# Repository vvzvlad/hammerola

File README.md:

# hammerola

**English** · [Русский](README.ru.md)

A build system and a viewer for parts that an agent models in code. The agent
writes a `model.py` in CadQuery and pushes the source; the hub computes the
geometry and shows the part in a browser. The person turns it, hides what is in
the way, cuts a section through it, measures it, downloads it as STEP/STL/3MF,
clicks a spot on the model and leaves a note there; the agent reads the notes
with `hammerola comments`, fixes the code and pushes the next revision. No CAD
application is needed anywhere: the model is Python, and the kernel that
computes it is in the hub.

The viewer is there because an STL an agent hands back is a poor thing to
review, and words are a poor way to say what to fix. The page gives what a CAD
gives — each part in its own colour, a section through anything, parts you can
drag aside — and a place to point at: the comment is pinned to that point, with
the camera angle it was written from and, when there is one, a photo of the
printed part. A revision's URL never changes and never expires, so a link is
how a part is shown to someone or sent to a workshop. What goes with the part
publishes on the same page — a KiCad schematic and board with the board's
Gerbers, a PDF, a drawing, a Markdown note, or a file of any other kind — and a
project with no model at all publishes those on their own. The name is from
"pianola" — a mechanism that plays itself.

<!-- Screenshots live in docs/images/ rather than in static/. static/ is the
     viewer payload that ships INSIDE the image, and its `hammerola*` names are
     generated and gitignored; README pictures are drawn by the forge straight
     out of the repository and have no business in a container. -->

## How it works

A model is a directory with a `model.py` in it, in a git repository. A version
of it is a commit: `git push` sends it to the project's own repository on the
hub, which **computes the geometry itself** — in a process of its own, with the
CAD kernel that ships in its image — checks the result, exports STEP/STL/3MF
and serves the whole thing at a URL, and only then lets the push in. Nothing is
built on the laptop, and no forge's CI is involved. A directory with no
`model.py` that lists documents in its `project.json` is published the same way,
except that nothing in it is executed: the documents are the whole build.

Four things follow from that, and between them they are what the tool is for.

**A revision is a commit, and a failed build is a refused push.** The author
pushes the whole repository; the project is the directory holding a
`project.json` with its id, so one repository can carry several projects, each
pushed to its own address. Of each push the hub builds the newest commit that
touched the project's directory, publishes it under the commit's sha and only
then lets git move the branch — a build that fails refuses the push, with its
log in the output, so the branch on the hub never stands on a commit without a
build. Builds published before the hub spoke git were imported into that
history as commits of their own, under their old names.

**A published revision never changes and never expires.** Its URL is served as
immutable, and there is no retention anywhere on the hub — nothing ages out and
no build can be taken back on its own — so a link pasted into a chat shows the
same geometry a year later. `dev` is the other kind of slot: one per variant,
rewritten by every `hammerola build`, no history, never listed, and it is where
the working copy goes while a part is still moving — uncommitted, as a draft
the client pushes beside the branch.

**A variant of a project is a branch.** A ceiling and a wall version of one
case are two branches of its repository, each with its own history, `latest`,
draft and documents, and the page switches between them by the project's title,
for a reader with a link as much as for the owner. `main` is the default
variant and keeps the project's addresses; another branch `b` is under
`/project/<pid>/v/<b>/`, labelled by the `"variant"` key of its own
`project.json`, or by its name.

**Geometry that fails the gate is not published.** Every printable has to be a
valid solid with positive volume, export a watertight mesh and come out as one
body. The `assembled` view is required, it has to show every printable unless
it lists one in `absent_ok` with a reason (an assembly jig is printed but is not
part of the product), and no two parts in it may occupy the same space unless the view says why — with one
standing exemption that is not a declaration: a `mock` is scenery, so a pair
holding one is never measured at all, while `hardware` is asked like anything
else. The `print` view is the bed: printables only, each of them the way up the
catalogue holds it, and each on its own patch of it rather than modelled inside
its neighbour. A build that fails any of it is thrown away whole — `latest` and
`dev` do not move — and what comes back is a failure code and the build's own
log.

**The model is public, the files go with a link that includes them, and the
code is not.** A build's page and the geometry it is drawn from are anonymous:
being given the link is what lets you look at the part. Its STEP/STL/3MF leave
only with the one secret or with a link the owner's Share window made with the
files included. Documents are the exception, on purpose: every file a project
lists as one opens to the link alone, whatever its extension, because that link
is how a revision goes to a workshop or a fab as the complete set — so whoever
has it can download a listed KiCad design whole and edit it. The repository a
revision was built from is on the hub too, but behind the secret, and so is the
list of what exists on the hub at all.

## Publishing a model

The client is `hammerola`, and it lives in this repository on purpose: the
client and the hub share one contract — the routes, the ceilings, the job
states — and it used to be split across two repositories
where no test could see both halves, which is exactly how publication came to be
broken without anyone noticing. It imports nothing outside the standard library,
so whatever `python3` a laptop already has is enough.

**It is installed from the hub**, which serves the three things a first run
needs and asks for no token for any of them — they are the software, identical
on every deployment, and the person downloading them does not have a token yet
by definition:

```bash
mkdir -p ~/.local/bin
curl -fsSL <hub>/start/hammerola -o ~/.local/bin/hammerola && chmod +x ~/.local/bin/hammerola
hammerola login <hub>   # once per machine; the password is prompted for, then the
                        # agent instructions go into ~/.claude/skills/hammerola/
```

The instructions are a directory — a short `SKILL.md` an agent keeps in front of
it and reference files it opens when they apply — so the client installs them
rather than a `curl` per file: it writes the whole directory and removes what
the new version no longer ships.

**On a machine where the client is already installed, that `curl` line comes
first.** A client from before the skill was a directory downloads the archive
and tries to read it as text, and its refusal blames the hub for serving
something that is not utf-8; it is that client being older than the hub, and
replacing it (the `curl` above, or `hammerola update`) is the way out.

**That is how it is installed, checkout or no checkout.** There used to be a second
one — `make client`, which symlinked a `bin/hammerola` script into
`~/.local/bin` — and the two collided under the one name they share: `curl -o`
writes THROUGH a symlink, into its target, so the line above quietly landed the
downloaded zipapp on top of the repository's own file. The link stayed a link,
the command went on working, and the only sign was `git status` calling the
client modified. Both the target and the script are gone. Whoever is *working
on* the client runs it out of the checkout instead — and the whole trick is that
`python3` has to be able to import `hammerola`, which is a statement about where
the command is STARTED, not about where the model is:

```bash
cd <this checkout>
python3 -m hammerola --help                          # the same tool, off the working copy
python3 -m hammerola -C <model dir> status           # the model directory is an argument
```

`-C` exists because nothing here is installed by default to run from inside a
model directory: `python3 -m hammerola` started there fails with
`No module named 'hammerola'`, and so does `python3 -m hammerola status` started
in the checkout — the tool resolves, and then finds no `project.json`. The other
way round works too, if the shell is already in the model:

```bash
PYTHONPATH=<this checkout> python3 -m hammerola status
```

No venv and nothing to build either way: the package imports the standard
library and nothing else, which is the same property that lets the hub ship it
as one file.

The downloaded client is a zipapp built out of `hammerola/` — one file, nothing
installed, python 3.9 and up (`src/onboarding.MIN_PYTHON`, which is also what
the skill tells the reader and what a test holds the syntax to: a stock
`/usr/bin/python3` is 3.9 on macOS and on Debian 11, so "newer than that" is a
first onboarding step that fails on the ordinary machine).

`GET /start` is the manifest that names both of those, plus the starter template
`create` fetches below — and one boolean, `empty`, which is the only thing on
this service that says anything about the deployment without the token. It is
deliberately never a count, a name or a date, and it fails closed: a project
directory the hub cannot read answers "not empty", rather than telling somebody
their hub is empty on the strength of an error. It is what the SIGN-IN PAGE of a
hub nobody has pushed to reads: instead of a login form and nothing else, it
draws five lines to hand an agent — what this hub's address is, the command
that installs the client, the one that logs in and installs the skill, read the
skill and follow it, ask the owner for the token. The addresses in it are built
from the browser's own origin and the manifest's paths, so nothing here names a
deployment; the request is made only
when the form is what is on the screen, and every failure of it is silence.
`hammerola create` is the other reader, and it follows `template`. The manifest
also states the DIGEST of the skill this image ships, a sha256 over its files
that `hammerola skill` compares with the same digest of a laptop's copy, and the
VERSION of the client it serves, which is what `build` compares itself against
before it publishes; like the three paths both are constants
of the image and say nothing about the deployment.
`src/onboarding.py` carries the argument for the boolean and for why it is
never a count.

Then, in the part's own directory — named first, because the name is what
`create` reads:

```bash
mkdir t13-ceiling-mount && cd t13-ceiling-mount                    # the directory names the project
hammerola create --title "T13 ceiling mount (t13-ceiling-mount)"   # once: project.json + template
git init -b main && git add -A && git commit -m "start"            # a version is a commit
hammerola connect                                                  # once: the remote hammerola-<pid>
hammerola build                                                    # publish the working copy into `dev`
git commit -am "thicker plate" && git push hammerola-<pid> main    # publish an immutable revision
```

`create` fetches the starter template from the hub and unpacks it beside the
`project.json` it mints — a `model.py` that builds as it stands. It never writes
over anything that is already there, and `--no-template` is the form for a
directory that already has a model, or for a machine with no hub to reach: the
id has always been minted locally and still is.

The title ends with the directory's own slug in brackets, and `create` writes
that slug into `project.json` as a third key, `project` — the latin name the hub
publishes under, on the index card and in the build page header. It is decided
here because here is the only machine where it exists: a push is unpacked on the
hub under a name of the hub's own, so a build that worked the answer out for
itself would name the project after that.

`connect` adds the remote `hammerola-<pid>`, includes from the repository's own
config the file `login` wrote the hub's password into for git, and — for a
project published before git — joins the hub's history into the local `main`
with a merge that changes no file. It prints the push for the branch checked
out: `git push hammerola-<pid> <branch>` publishes a revision of that branch's
variant, and `hammerola build` writes the draft of that branch — of `main` into
`/project/<pid>/dev/`, of any other into `/project/<pid>/v/<branch>/dev/`. A
branch name is letters, digits, `-` and `_`; the hub refuses any other. A
pushed branch stays a variant until `git push --delete hammerola-<pid>
<branch>` removes it with every revision no other variant has; `main` cannot
be removed this way.

Both ways of publishing are a `git push` that waits for the build and prints
what the build printed: `git push hammerola-<pid> main` publishes a revision,
and `hammerola build` commits the working copy through an index of its own —
the author's index and history untouched, what git ignores left out — and
pushes it as the draft. The exit code is the point, because it replaces a
forge's job status: zero means a build was published, and a refused push, a
model that raised, a gate that said no and a hub that could not be reached are
each non-zero with the sentence that says which.

The rest of the commands answer questions about a project that is already there:

```bash
hammerola status                 # latest, dev and the revisions of this branch's variant, and the variants
hammerola log <revision>         # read a build log again
hammerola artifacts <revision>   # its STEP/STL/3MF and its documents
hammerola diff <rev> <rev>       # what moved, in geometry and in source
hammerola comments               # notes left on this project's builds
hammerola proposal               # the edit the viewer's reader proposed, as code
hammerola rename "New title"     # the title, never the id
hammerola skill                  # is the installed agent skill current?
hammerola skill update           # write the hub's copy over it
hammerola update                 # replace THIS TOOL with the hub's copy
```

`skill` and `update` are the odd ones out: they ask about this MACHINE rather
than about a project. `skill` exists because the skill is the only thing here
that goes stale in silence — a client that is behind is refused by its own
`build` and told what to run, while a stale skill goes on confidently teaching a
command that no longer exists. It compares a digest of the installed files
against the one the hub states in `/start`, so any change to any file of the
skill shows, and only ever writes when `update` was typed.

`hammerola update` is the same move one level down: it fetches the client the
hub serves and writes it over the file it is running from — checked first, since
what lands there is what the machine will run next, and written through a rename
so an interrupted update cannot leave a laptop with no tool and no way to fetch
one. It then prints what changed between the two versions, which is what makes
the refusal above worth acting on rather than merely obeying. There is no flag
for where to write: a copy running out of a checkout is told to use git.

`hammerola --help` has the flags, and `hammerola rm` — the one command that
unmakes anything. It removes a project whole, never a single build, and it asks
for the id to be typed first.

## What a model.py looks like

<!-- THE EXAMPLE BELOW STAYS, AND SO DOES model_template/. An earlier note here
     asked for this block to be replaced by a pointer to the template the day
     the template landed (issue #31), on the argument that a contract
     must have ONE source or the second copy drifts in silence. The template
     has landed, and the argument does not apply: NEITHER COPY CAN DRIFT,
     because both are executed. This block is lifted out of README.md and
     built the way a push is built (tests/test_readme_example.py), and
     model_template/ is a working project run through the same build path
     (tests/test_template.py). Two copies that are both built are two copies
     that are both true.

     They are also for different readers. The template is where a project
     STARTS — `hammerola create` fetches it from the hub and unpacks it — and
     it is 12 KB of commented model. This one is short enough to read on the
     repository page without downloading anything, which is what somebody
     deciding whether to use the tool at all is doing.

     So do not delete either, and do not delete tests/test_readme_example.py:
     it is the only thing holding this block to the contract, and because the
     block is now meant to stay, that test FAILS rather than skips if the block
     goes -- a skip nobody reads is not a test. -->

Start a project from the template — `hammerola create` brings it, and it builds
as it stands. What follows is the same contract at a size that can be read here
without downloading anything.

Three functions and one import are the whole contract. `parts()` is the
catalogue — every part of the model under the name it is known by, and where
its geometry lives; `views()` says what the viewer shows, one tab per
view, each of them a list of references into that catalogue; `checks()` is
optional and holds this part to its own numbers. The geometry comes from
`cadquery`, and the shared checks from `checklib` — the third bullet below says
what that one carries.

**And every number in it says where it came from**, which is a ground a push is
refused on and not a convention: a module-level `UPPER_SNAKE` name bound to a
plain float stops the build. `checklib.measured`, `derived` and `estimated` are
how it says which. `estimated` always builds, so this is a rule about SAYING
rather than about measuring — most of a first model is honestly a set of
choices, and the log lists them. `measured` is the one with a cost attached: its
source has to name a file that exists in the project, and — if it names a
heading after a `#` — a heading that is really in that file. How
many of each kind a build declared reaches `metrics.json` exactly, and so do the
notes and the names of the estimates — each list up to the first 256 of them,
after which the file says how many it left out rather than growing without a
ceiling.

```python
"""A flat mounting plate: one printed part, driven by the numbers at the top."""

import cadquery as cq

import checklib

# Every number says where it came from, and the build refuses one that does not:
# `measured(v, "file.md#heading")` for a figure somebody took, `derived(v, why)`
# for one that follows from others, `estimated(v, what_would_settle_it)` for one
# nobody measured. The last always builds, and the log says which numbers it was.
LENGTH = checklib.estimated(60.0, "along X; whatever this bolts to settles it")
WIDTH = checklib.estimated(40.0, "along Y; the same")
THICKNESS = checklib.estimated(4.0, "of the plate; settled by bending one")
HOLE = checklib.derived(5.5, "M5 clearance, ISO 273 medium")
HEAD = checklib.derived(8.5, "M5 socket cap head diameter, ISO 4762")
INSET = checklib.estimated(8.0, "hole centres in from each edge; chosen to "
                                "look right")

def hole_centres():
    x, y = (LENGTH - 2 * INSET) / 2, (WIDTH - 2 * INSET) / 2
    return [(sx * x, sy * y) for sx in (-1, 1) for sy in (-1, 1)]

def plate():
    return (cq.Workplane("XY").box(LENGTH, WIDTH, THICKNESS)
            .faces(">Z").workplane()
            .pushPoints(hole_centres()).hole(HOLE))

def parts():
    """The catalogue, and the one place the geometry lives.

    The key is the part's identity everywhere: the stem it is exported under
    and the name a view points at. The label is DERIVED from it rather than
    equal to it — the exported tree tells repeats of one key apart (`pin`,
    `pin(2)`), and the tree a reader sees puts adjacent repeats back on a
    single counted row (`pin ×4`).
    """
    return {"plate": {"shape": plate(), "kind": "printable"}}

def views():
    """One tab each, and every entry is a REFERENCE into the catalogue.

    `assembled` is the product, `print` is the bed. They hold the same list here
    only because there is one part: a single part is already its own bed layout.
    With two, `print` is where you move them apart with `at`, and the gate
    refuses a `print` view whose parts overlap.
    """
    return [
        {"id": "assembled", "name": "assembled", "parts": ["plate"]},
        {"id": "print", "name": "as printed", "parts": ["plate"]},
    ]

def checks():
    """Optional. Measure the solid rather than restate the numbers above.

    It may take one argument — the directory the build has already exported
    into — for a check that reads the files instead of the geometry.
    """
    part = plate()
    holes = part.faces("%CYLINDER").vals()
    assert len(holes) == 4, f"the plate has {len(holes)} bores, not 4"

    # The shared version of "the screw head has something to bear on". The box
    # is centred, so the seat is the top face at +THICKNESS/2 and the head has
    # the whole plate under it. A check may also report by returning strings.
    problems = []
    for x, y in hole_centres():
        problems += checklib.material_under_head(
            part, (x, y, THICKNESS / 2), HEAD, THICKNESS, name="plate")
    return problems
```

Beside `project.json`, which `hammerola create` writes, that file is the whole
project. Four things about it are worth knowing before writing the second one:

* **A catalogue entry needs `shape` and `kind`; `color` and `note` are
  optional.** `kind` is `printable`, `hardware` or `mock` — what you print, what
  you buy, what is only there so the picture makes sense — and it has no
  default, deliberately: defaulting to `printable` would export a mock of a
  bought bearing and put download buttons under it. An entry that names no
  colour is painted by its kind, so the picture says by itself what goes on the
  bed and what was bought. A VIEW HOLDS NO GEOMETRY, AND HAS ONE DOOR:
  `"plate"` is the part as the catalogue has it, `{"part": "plate", "at": <a
  cq.Location>}` is the same part placed, and `alpha` goes there too — while
  `{"part": "strap", "shape": bent, "deformed": "clamped round the pipe"}` is
  the one way a shape reaches a view at all, for a part that really is a
  different shape in place. The reason is required and is printed into the
  build log, because an unexplained second shape under a part's name is the
  look-alike this whole design refuses; and the plate will not take one, there
  being no "in place" on a bed.
* **`checks()` runs on the hub, and a demonstrably empty one is refused.** The
  build counts the checks in the function's own source, and refuses a body with
  no assert, no raise, nothing filling the list it returns and not so much as a
  call in it — a function that passes for that reason is worse than no
  function. A body it cannot count is not refused: a comprehension, a table of
  checks or a helper handed the problem list gets `count unknown` in the log
  and publishes.
* **`import checklib` is part of the contract**, next to those three names: it
  carries the checks that keep coming up — every pair of parts checked for
  shared volume, a mating face that has to stay flat, material under a screw
  head — so a fix to one of them reaches every project instead of one.
* **Dependencies come from the image and nowhere else.** Nothing is installed on
  a model's say-so, so `model.py` imports what the hub already has: `cadquery`,
  `checklib`, the standard library, and whatever the project ships beside it.

## Documents: boards, drawings and any other file

A part rarely travels alone: there is the board inside it, the cut list, the DXF
for the glass shop, the datasheet of the amplifier. A project publishes those as
DOCUMENTS — files of its tree that `project.json` lists, in the order the page
shows them:

```json
"documents": ["docs/cut-list.md",
              {"file": "hw/main.kicad_sch", "title": "Main schematic"},
              {"file": "hw/main.kicad_pcb", "title": "Main board"},
              {"file": "hw/main.glb", "title": "Main board, 3D"},
              {"file": "fab/main-gerbers.zip", "title": "Gerbers"},
              {"file": "cut/glass.dxf", "title": "Glass, cut list"},
              {"file": "ds/tpa3250.pdf", "title": "TPA3250", "hidden": true}]
```

Nothing is picked up by extension: a file is a document because the list names
it, and it is published under its own path, so a link between two of them works
as it does in the tree. An entry is the path, or an object with the path as
`file`, a `title` the page shows in its place, `"hidden": true` for a file that
is published and opens by its address but has no row in the menu (twenty
datasheets are twenty hidden entries, not twenty rows), and `"download": true`
for a file to be taken rather than drawn (a text file is shown as text all the
same: the page knows it by its extension). On a model's page the documents follow
the views in the same menu: choosing one shows it over the model, choosing a
view brings the model back, and `?d=<id>` in the address opens one on arrival.
Whatever document is open, Download and Copy link for its file stand at the
bottom left of the page. A project with no `model.py` — `hammerola create
--no-template` starts one — is built out of its documents alone, and its page is
the same menu with no model behind it.

**The extension decides only how a document is shown.** Markdown is drawn, and
a link in it to another listed document opens that document on the page; a PDF,
a picture, HTML and SVG are shown as they are; a CSV is drawn as a table, its
first row the header, and any other text file — `.txt`, `.tsv`, `.json`, `.xml`,
`.yaml`, `.yml`, `.toml`, `.ini`, `.log` — as its text, in monospace;
`.kicad_sch`, `.kicad_pcb`, `.glb` and `.zip` are the board, below. A file of
any other extension — a supplier's STEP, a firmware image — is a plain file:
choosing it shows its name, extension and size instead of drawing it. A
`.dxf` is a plain file with a picture: the hub draws an SVG of it when the push
is checked, publishes it at `<path>.svg`, and the page shows that picture above
the file's name and size.

**A KiCad board is up to three documents with one name.** A schematic, its board
and the board's 3D model whose paths differ only by the extension are one
design. The schematic is listed by its root sheet and brings every sheet it
names, either of the two brings the `.kicad_pro` beside it, and the `.glb` is
made on the laptop with
`kicad-cli pcb export glb`, not on the hub. The views are linked: a part clicked
in one is selected in the others. A right click on a part, a pad or a net in any
view, and on the schematic a left click on a net too — a label, a power symbol,
a sheet pin, a wire — opens one menu: a row for every place it can be shown —
under `PART C507` the part in each view and its datasheet, under `NET +12V` every
place of the net on every sheet and the net on the board.
The menu opens on the row of what was clicked; the arrows ‹ › step from place to
place and a click on a row goes there, switching the view or the sheet, and the menu
stays open.
A part has a datasheet when its `Datasheet` field names a PDF the project lists
(`${KIPRJMOD}/ds/tpa3250.pdf`, hidden above): its row opens the PDF in a window
over the design. The board view has its own panel of layers and lights the whole
net of a clicked track or pad; the 3D view turns like the model does.

**The Gerbers are one zip**, drill files included — what goes to the fab. The
page unzips it in the browser, tells each layer by its `%TF.FileFunction`
attribute rather than by the file's name, and draws copper, mask, silkscreen,
paste, outline and drills with a toggle per layer, from the top or from the
bottom. A
`.zip` is read as Gerbers unless its entry says `"download": true`, which is how
a zip of stand logs stays a plain file.

**A wrong list refuses the push, whole.** A path that is not a file, a path
listed twice, a file that would overwrite what the model's build wrote, a DXF
the hub cannot draw, a missing sheet or one outside the project — each is a 422
naming the entry, and nothing is skipped in silence. The complete rules, with
the `kicad-cli` lines for the 3D model and the Gerbers, are written for the
agent that lays a project out: `skill/references/documents.md` and
`skill/references/boards.md`.

## Running a hub

**A hub is one Docker image, and everything it needs is inside it.** That is not
packaging convenience, it is the architecture: the CAD kernel is in the image
(`cadquery` and the native OpenCASCADE binding, with the seven X/GL/expat system
libraries it needs), and nothing is ever installed on a model's say-so — a
`model.py` gets what the image already has and nothing more. The browser bundle
is compiled in a `node:22` stage that never reaches the runtime image, so a
service that is Python does not ship a node toolchain. Alongside them travel the
page templates, the viewer payload, the starter template and the client's own
sources: the one-file zipapp behind `/start/hammerola` is assembled out of those
when the request arrives.

CI builds and publishes it — `.gitea/workflows/image-check-publish.yml`, on every
push:

```
gitea.vvzvlad.xyz/projects/hammerola:latest     # main, what a deploy pulls
gitea.vvzvlad.xyz/projects/hammerola:<sha>      # main, the rollback point
gitea.vvzvlad.xyz/projects/hammerola:<branch>   # anything else
```

`:latest` is pushed LAST of the two, so it moving is the commit of the whole
publication: if `:<sha>` fails to reach the registry the run stops before
`:latest` moves, and what is deployed keeps running the previous image. Only
`main` ever writes `:latest` — a side branch publishes under its own name and
cannot overwrite what production pulls. Do not count on every commit having a
`:<sha>`: a run still queued when the next push lands is cancelled, and with a
build measured in tens of minutes that is ordinary rather than exceptional.

Between the build and the push sits a gate,
`ci/smoke.py`, which starts the image and asks it what a test suite structurally
cannot, because the suite runs against a checkout and never looks at the
artefact: that the entrypoint drops privileges for real, that the
missing-variable guard fires and names the variable, that `.dockerignore` kept
the tests and the `.env` out, that the CAD kernel imports, and that `/start`
really answers. Nothing reaches the registry until it is green, which is also
why `docker login` runs *after* it and never before.

Locally the same image is a plain build with no arguments — but expect it to be
big and slow. The CAD kernel brings VTK with it, hard-pinned by `cadquery-ocp`
itself, and that alone is about 0.6 GB the hub never renders with; it is carried
anyway, because the only way out is substituting a different distribution behind
the declared dependency, and that trade was decided against.

```bash
docker build -t hammerola .
```

**Deploying is `docker-compose.yml` in this repository** — a template with
placeholder values that pulls `gitea.vvzvlad.xyz/projects/hammerola:latest`. Do
not build on the host that serves it. Four things in it are load-bearing rather
than decorative, and each one is spelled out at length in the file itself:

* **One volume at `/app/data`.** Every build, pointer, repository, comment and
  job lives there; nothing ages out, so it grows monotonically and is cleared by
  hand. The volume's real name is `<stack>_<key>`, composed at deploy time —
  getting it wrong does not fail, it silently starts the service from a fresh
  empty one with all the state still sitting in the volume nothing references.
* **One secret, `EDIT_TOKEN`.** It is what publishing, the repositories, the log, the
  comment queue, renaming and removing all check; everything else has a default
  in `src/settings.py`. Without it the service refuses to start and says which
  variable is missing, rather than coming up half-configured.
* **Non-root, by the entrypoint and not by the Dockerfile.** It starts as root,
  fixes ownership of the volume and drops to `app` (uid 1000) with gosu. Nothing
  declares a `USER`, so removing the entrypoint silently gives the service root
  back — which is exactly why the gate checks it on the built image.
* **No `EXPOSE`, and compression at the edge.** The port is published by the
  reverse proxy through compose labels, and so is gzip: a view is JSON in the
  megabytes that compresses about 6.5×, and the application deliberately does
  not compress anything itself. The healthcheck's timings are part of the deploy
  mechanism too — an update that cannot report healthy inside its window is
  rolled back, and a long `interval` with no `start_period` gets a perfectly
  good image rolled back for nothing.

**Working on the hub is the other mode**, and it needs no docker at all.
Everything routine is wrapped in the `Makefile` (`make help` lists all targets):

```bash
make install                # create .venv + install dev/test deps
cp .env.example .env        # fill in the values
make test                   # run tests
make run                    # run the app
```

Python targets create and reuse a local `.venv` automatically — you never need
the system Python. node is needed by the frontend targets only: `make ui`,
which builds the browser bundle, and `make ui-test`, which runs the JS suite.
Both refuse to run without npm. `make test` does not refuse — it runs the
Python suite either way and then says out loud that it skipped the browser
half. What `make run` cannot give you is the CAD kernel unless the machine
happens to have it: a workstation without it serves every page and refuses every
build, which is the one thing the image is there for.

## Where the rest is written down

| File | What it holds |
| --- | --- |
| `AGENTS.md` | The rules themselves, stated in one line each, and where to read the rest. It is deliberately short: it is loaded into every agent's context, so the reasoning lives in the three files below it. Start here before changing anything. |
| `docs/conventions.md` | The same conventions with the reason each one exists — usually the thing that broke silently before it was written down. |
| `docs/repo-map.md` | What every directory and every load-bearing file in this repository is for. |
| `docs/SPEC.md` | The requirements, the facts that were verified the hard way, and the work plan. |
| `ui/README.md` | The browser interface: its layout, its pins, and why it is built twice. |
| `docs/ui-brief.md` | What the interface is FOR: the reading the panels are built around, and the vocabulary they use. |
| `docs/viewer-api.md` | The vendored `three-cad-viewer`: what of it is a public API, and what the viewport reaches into at its own risk. |

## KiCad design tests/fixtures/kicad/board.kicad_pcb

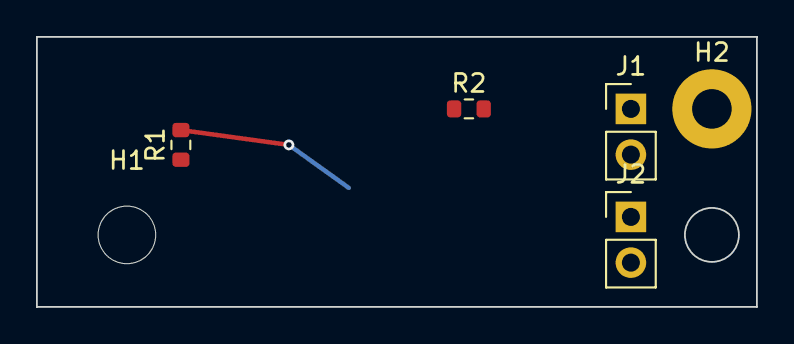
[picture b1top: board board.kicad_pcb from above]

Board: 2 copper layers, 40.0 x 15.0 mm, 7 parts (1 on the bottom side), 3 nets.

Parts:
C1: C_0603_1608Metric
H1: MountingHole_3.2mm_M3
H2: MountingHole_2.2mm_M2_Pad
J1, J2: PinHeader_1x02_P2.54mm_Vertical
R1, R2: R_0603_1608Metric

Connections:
GND: C1.2, J1.2, J2.2, R2.2
SIG: C1.1, R1.2
VCC: J1.1, J2.1, R1.1, R2.1
